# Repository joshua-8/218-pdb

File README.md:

# archived, moved to https://github.com/SPDLDaemon/SPDL-PDB

# Smart Product Design Lab - Power Distribution Board v2.1
## features
* 16 JST XH plugs with 3.3v ground and 5 volts
* 8 molex 254 plugs for servos

## user guide image

#### [link to user guide image](/218PDBguide.drawio.png)

### [link to schematic](/schematic.pdf)
### [link to image of PCB traces](/pcb.pdf)

## assembly
assembly guide coming soon

## images

## buying PCBs and components 
1x set of components from [bill of materials](/BOM.csv)

2x tamiya connectors for batteries (with wires)

1x main power switch

1x fuse holder (with wires) and fuse

1x PCB from ([gerber files](/gerbers.zip))

JST XH sockets (16)

JST XH crimps (48)

small flathead screwdriver

JST XH crimper

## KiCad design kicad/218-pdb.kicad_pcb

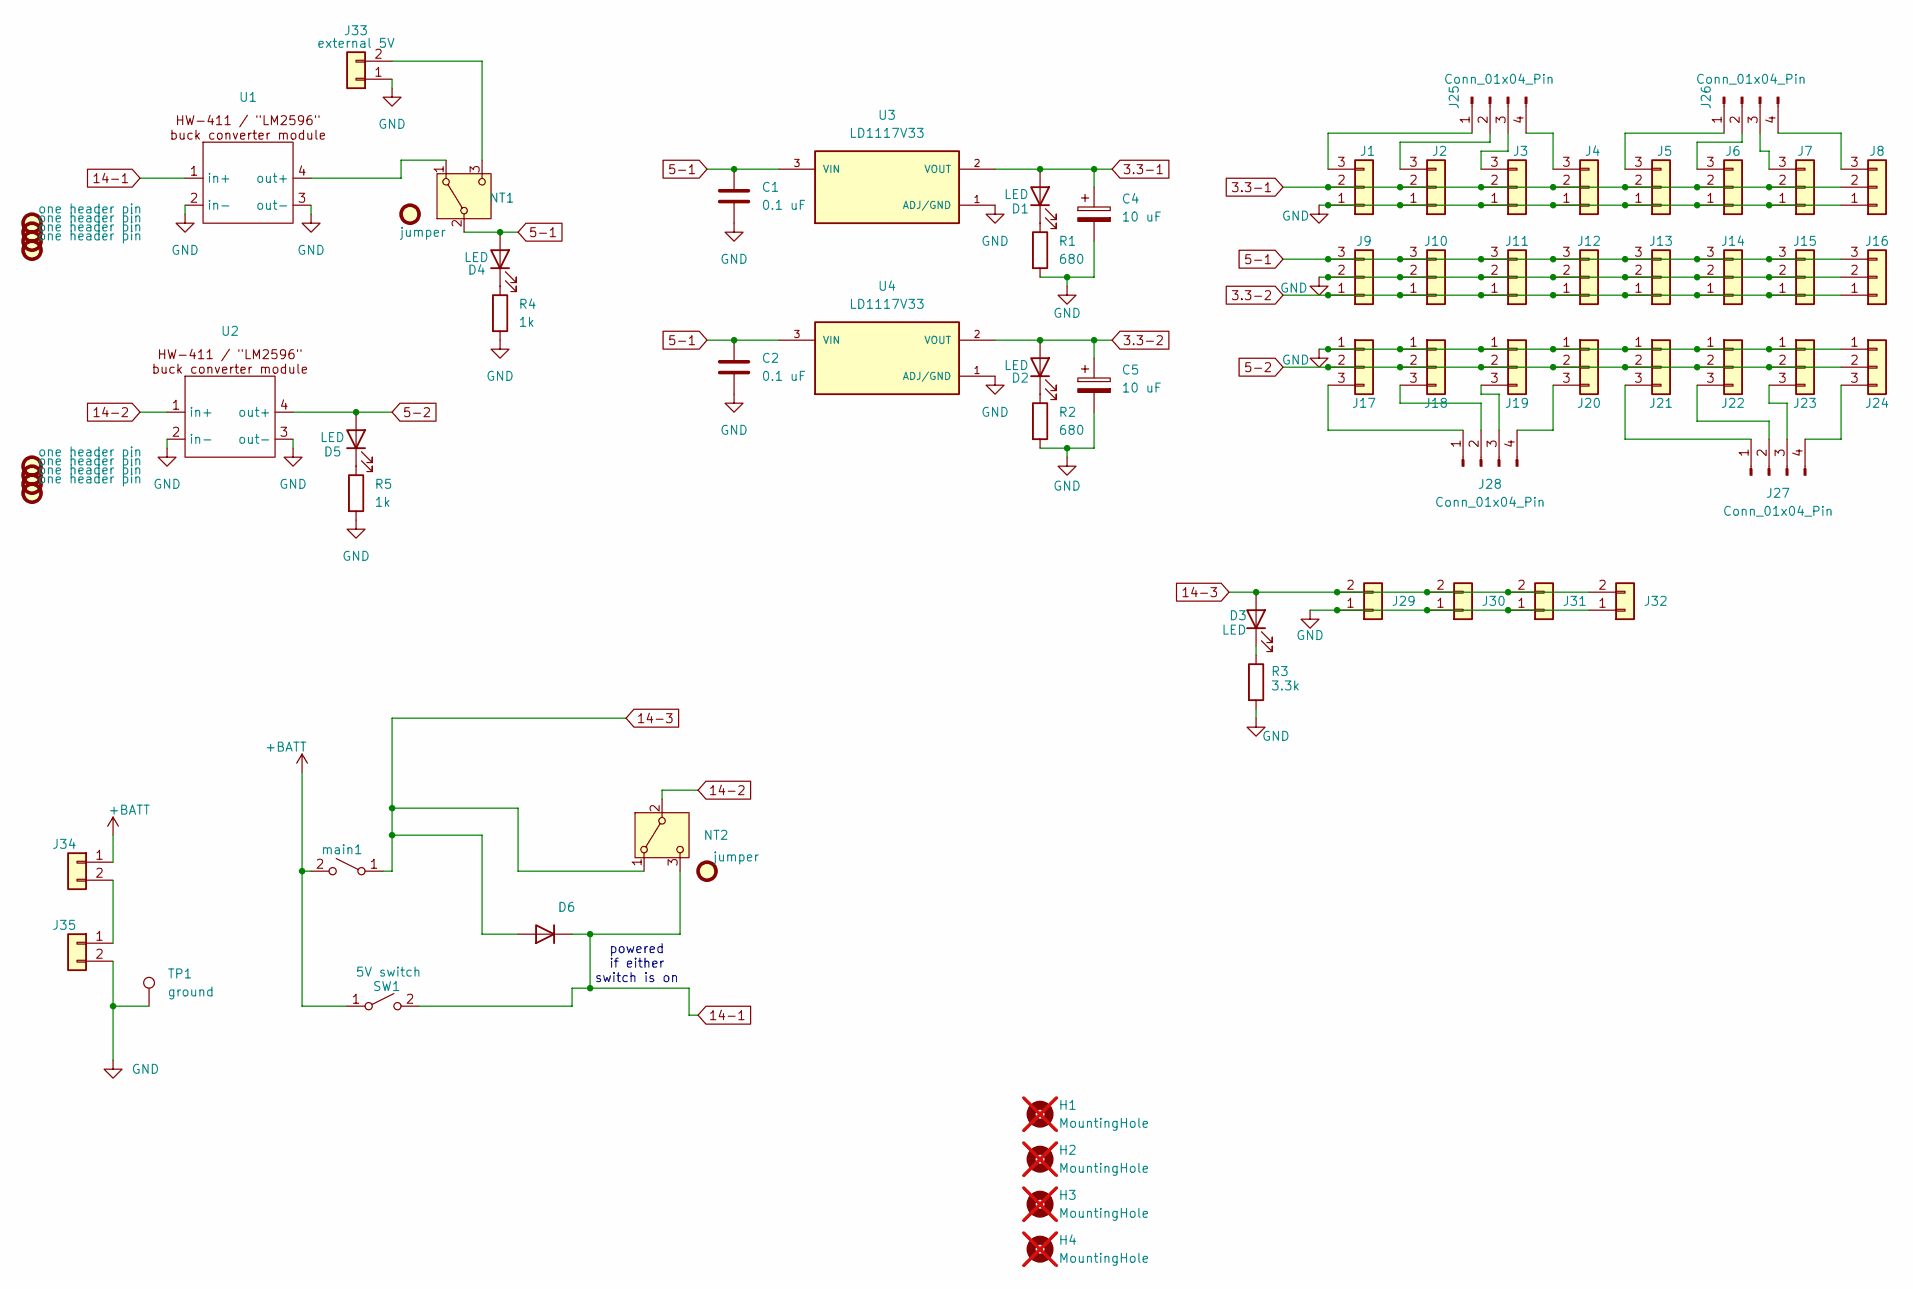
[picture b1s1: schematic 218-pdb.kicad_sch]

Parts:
C1, C2: 0.1 uF; C_Disc_D3.0mm_W2.0mm_P2.50mm; Part_Number 0.1 uF ceramic capacitor
C4, C5: 10 uF; C_Disc_D3.8mm_W2.6mm_P2.50mm; Part_Number 10uF tantalum (polarized) capacitor
D1, D2, D3, D4, D5: LED; LED_D3.0mm; Part_Number 3 mm diameter LED
D6: diode, >=1Amp; D_DO-41_SOD81_P2.54mm_Vertical_AnodeUp; Part_Number spdl, 1N4935
FID1, FID2: jumper; Part_Number pin jumper 0.1" pitch Sullins QPC02SXGN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
FID3, FID4, FID5, FID6, FID7, FID8, FID9, FID10: one header pin; PinHeader_1x01_P2.54mm_Vertical; Part_Number spdl, one header pin
H1, H2, H3, H4: MountingHole; MountingHole_3.2mm_M3_ISO7380; not fitted
J1, J2, J3, J4, J5, J6, J7, J8, J9, J10, J11, J12, J13, J14, J15, J16, J17, J18, J19, J20, J21, J22, J23, J24: Conn_01x03; Molex_KK-254_AE-6410-03A_1x03_P2.54mm_Vertical; Part_Number 3 pin KK254 molex 0022232031
J25, J26, J27, J28: Conn_01x04_Pin; PinHeader_1x04_P2.54mm_Vertical; Part_Number 4 header pins 0.1" pitch
J29, J30, J31, J32: 14 V molex; Molex_KK-396_A-41791-0002_1x02_P3.96mm_Vertical; Part_Number 2 pin KK396 molex 0026604020
J33: external 5V; Molex_KK-254_AE-6410-02A_1x02_P2.54mm_Vertical; Part_Number 2 pin KK 254 molex 0022232021
J34, J35: battery; CUI_TB007-508-02BE; Part_Number screw terminal, 5.08" pitch, TB007-508-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
NT1, NT2: PinHeader_1x03_P2.54mm_Vertical; Part_Number 3 header pins 0.1" pitch
R1, R2: 680; R_Axial_DIN0309_L9.0mm_D3.2mm_P2.54mm_Vertical; Part_Number spdl; digikey_part_number n/a
R3: 3.3k; R_Axial_DIN0309_L9.0mm_D3.2mm_P2.54mm_Vertical; Part_Number spdl; digikey_part_number n/a
R4, R5: 1k; R_Axial_DIN0309_L9.0mm_D3.2mm_P2.54mm_Vertical; Part_Number spdl; digikey_part_number n/a
SW1: 5V switch; SLW-12689-4A-N-D; Part_Number SLW-12689-4A-N-D
TP1: ground; TestPoint_Bridge_Pitch5.08mm_Drill0.7mm; Part_Number piece of wire
U1, U2: DC-DC buck; HW-411; Part_Number HW-411 lm2596 buck converter module; digikey_part_number n/a
U3, U4: LD1117V33; TO255P1020X450X1968-3; PARTREV 37; DigiKey_Part_Number 497-1491-5-ND
main1: MotorSW; CUI_TB007-508-02BE; Part_Number screw terminal, 5.08" pitch, TB007-508-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

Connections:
3.3-1: C4.1, D1.2 (A), J1.2, J2.2, J3.2, J4.2, J5.2, J6.2, J7.2, J8.2, U3.2 (VOUT)
3.3-2: C5.1, D2.2 (A), J9.1, J10.1, J11.1, J12.1, J13.1, J14.1, J15.1, J16.1, U4.2 (VOUT)
5-1: C1.1, C2.1, D4.2 (A), J9.3, J10.3, J11.3, J12.3, J13.3, J14.3, J15.3, J16.3, NT1.2 (B), U3.3 (VIN), U4.3 (VIN)
5-2: D5.2 (A), J17.2, J18.2, J19.2, J20.2, J21.2, J22.2, J23.2, J24.2, U2.4 (out+)
14-1: D6.1 (K), NT2.3 (C), SW1.2 (B), U1.1 (in+)
14-2: NT2.2 (B), U2.1 (in+)
14-3: D3.2 (A), D6.2 (A), J29.2, J30.2, J31.2, J32.2, NT2.1 (A), main1.1 (A)
+BATT: J34.1, SW1.1 (A), main1.2 (B)
GND: C1.2, C2.2, C4.2, C5.2, J1.1, J2.1, J3.1, J4.1, J5.1, J6.1, J7.1, J8.1, J9.2, J10.2, J11.2, J12.2, J13.2, J14.2, J15.2, J16.2, J17.1, J18.1, J19.1, J20.1, J21.1, J22.1, J23.1, J24.1, J29.1, J30.1, J31.1, J32.1, J33.1, J35.2, R1.2, R2.2, R3.2, R4.2, R5.2, TP1.1, U1.2 (in-), U1.3 (out-), U2.2 (in-), U2.3 (out-), U3.1 (ADJ/GND), U4.1 (ADJ/GND)
unnamed: D1.1 (K), R1.1
unnamed: D2.1 (K), R2.1
unnamed: D3.1 (K), R3.1
unnamed: D4.1 (K), R4.1
unnamed: D5.1 (K), R5.1
unnamed: J1.3, J25.1
unnamed: J2.3, J25.2
unnamed: J17.3, J28.1
unnamed: J18.3, J28.2
unnamed: J19.3, J28.3
unnamed: J20.3, J28.4
unnamed: J21.3, J27.1
unnamed: J22.3, J27.2
unnamed: J23.3, J27.3
unnamed: J24.3, J27.4
unnamed: J3.3, J25.3
unnamed: J4.3, J25.4
unnamed: J5.3, J26.1
unnamed: J6.3, J26.2
unnamed: J7.3, J26.3
unnamed: J8.3, J26.4
unnamed: J33.2, NT1.3 (C)
unnamed: J34.2, J35.1
unnamed: NT1.1 (A), U1.4 (out+)

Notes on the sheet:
powered if either switch is on

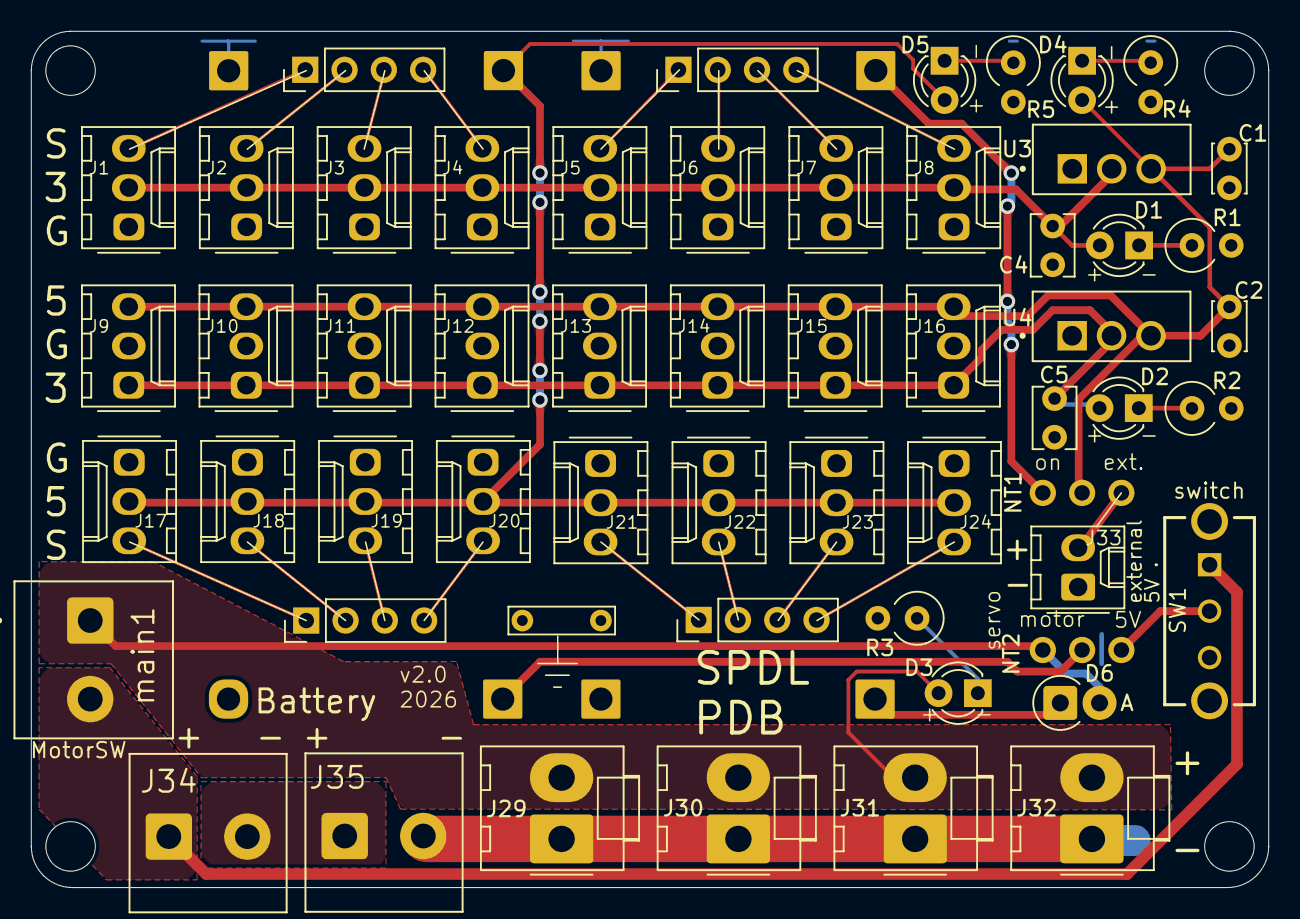
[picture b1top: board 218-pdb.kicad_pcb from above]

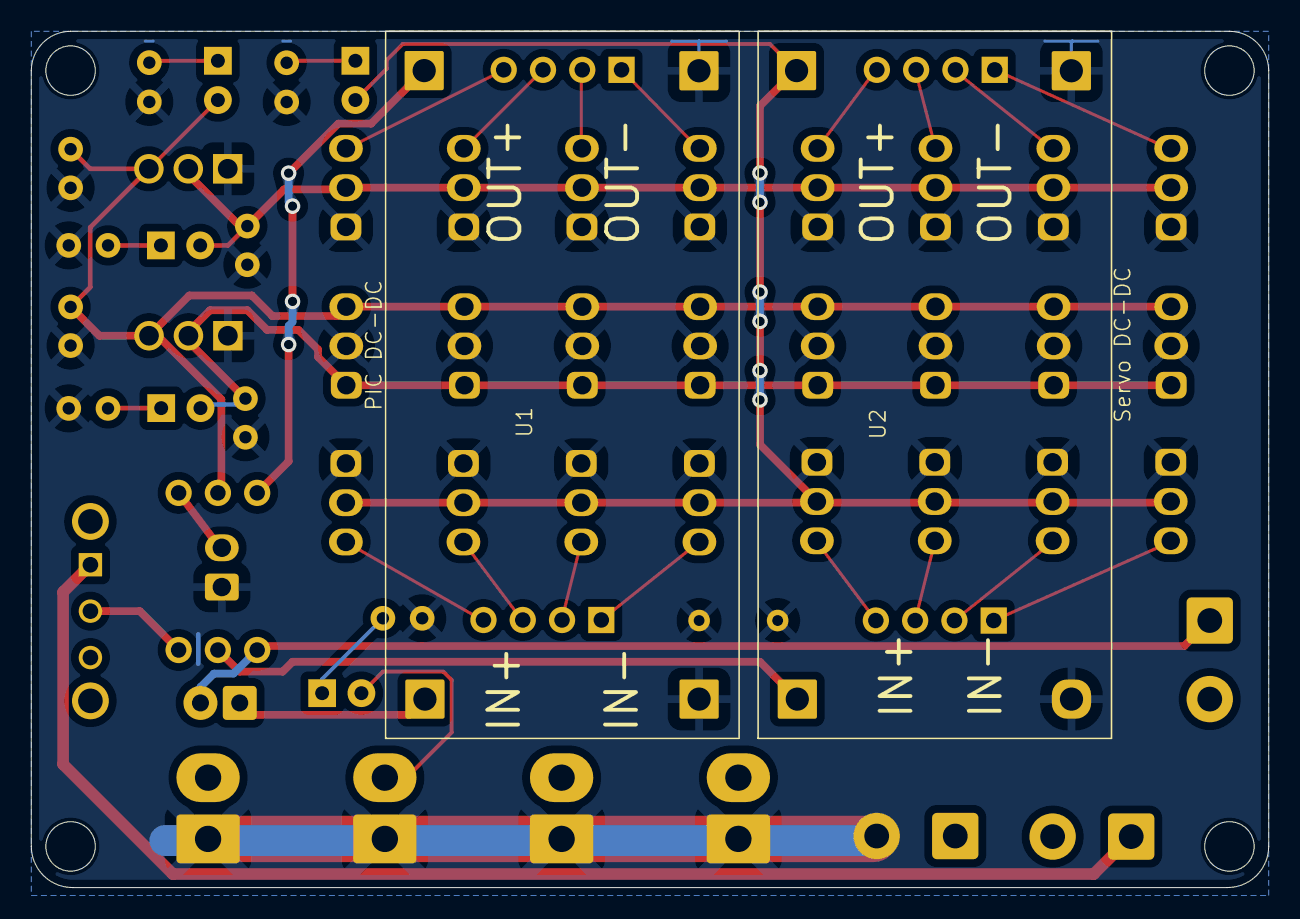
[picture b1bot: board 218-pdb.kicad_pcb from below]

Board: 2 copper layers, 80.0 x 55.4 mm, 73 parts (10 on the bottom side), 33 nets.

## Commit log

2026-01-01 edit schematic
2026-01-01 BOT process kicad
2026-01-02 draw traces, design B
2026-01-02 cleanup
2026-01-03 update script
2026-01-04 improve power traces
2026-01-04 rename folder
2026-01-28 Archive README and add new repository link
    Updated README to reflect archived status and moved repository link.
